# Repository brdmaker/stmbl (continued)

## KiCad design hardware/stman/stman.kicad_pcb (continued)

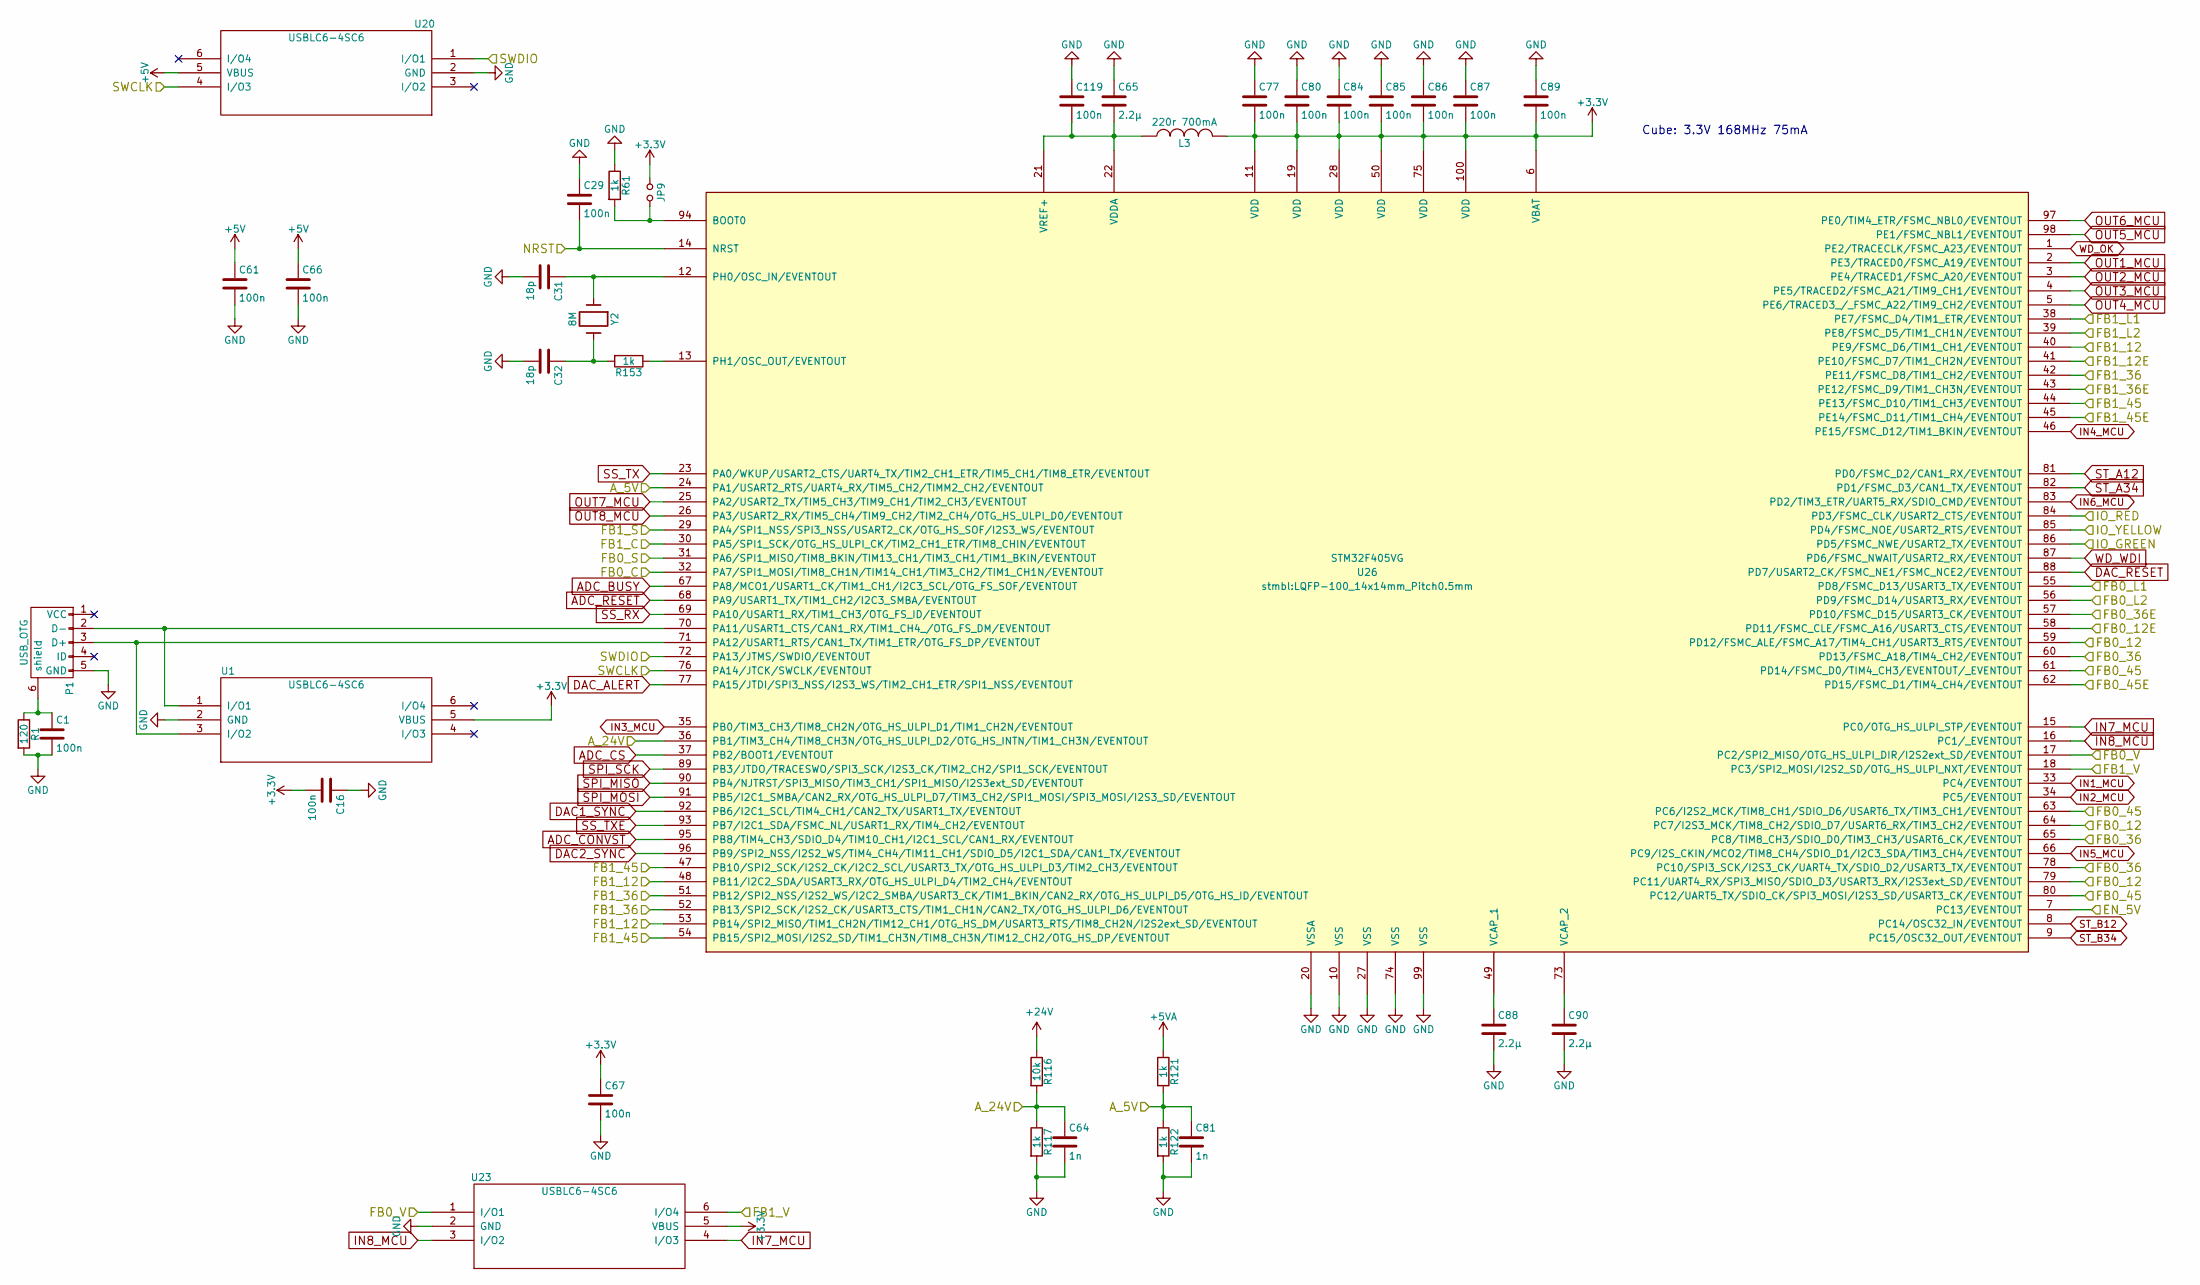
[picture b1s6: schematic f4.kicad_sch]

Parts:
C1, C16, C29, C61, C66, C67, C77, C80, C84, C85, C86, C87, C89, C119: 100n; C_0603; Voltage 50V; Tolerance X5R
C31, C32: 18p; C_0603; Voltage 50V; Tolerance X5R
C64, C81: 1n; C_0603; Voltage 50V; Tolerance X5R
C65, C88, C90: 2.2µ; C_0603; Voltage 35V; Tolerance X5R
JP9: Jumper_NO_Small; SOLDER_JUMPER
L3: 220r 700mA; R_0603
P1: USB_OTG; USB_Micro-B
R1: 120; R_0603; Tolerance 1%
R61, R117, R121, R122, R153: 1k; R_0603; Tolerance 1%
R116: 10k; R_0603; Tolerance 1%
U1, U20, U23: USBLC6-4SC6; SOT-23-6
U26: STM32F405VG; LQFP-100_14x14mm_Pitch0.5mm
Y2: 8M; Crystal_SMD_0503_4Pads

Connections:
+5V: C61.1, C66.1, U20.5 (VBUS); also elsewhere on the board
+5VA: R121.1; also elsewhere on the board
+24V: R116.1; also elsewhere on the board
/FB0/A12: U26.31 (PA6/SPI1_MISO/TIM8_BKIN/TIM13_CH1/TIM3_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); also elsewhere on the board
/FB0/A35: U26.32 (PA7/SPI1_MOSI/TIM8_CH1N/TIM14_CH1/TIM3_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); also elsewhere on the board
/FB0/A78: U23.1 (I/O1), U26.17 (PC2/SPI2_MISO/OTG_HS_ULPI_DIR/I2S2ext_S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); also elsewhere on the board
/FB0/D12: U26.59 (PD12/FSMC_ALE/FSMC_A17/TIM4_CH1/USART3_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), U26.64 (PC7/I2S3_MCK/TIM8_CH2/SDIO_D7/USART6_RX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), U26.79 (PC11/UART4_RX/SPI3_MISO/SDIO_D3/USART3_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); also elsewhere on the board
/FB0/D36: U26.60 (PD13/FSMC_A18/TIM4_CH2/EVENTOUT), U26.65 (PC8/TIM8_CH3/SDIO_D0/TIM3_CH3/USART6_CK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), U26.78 (PC10/SPI3_SCK/I2S3_CK/UART4_TX/SDIO_D2/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); also elsewhere on the board
/FB0/D45: U26.61 (PD14/FSMC_D0/TIM4_CH3/EVENTOUT/_EVENTOUT), U26.63 (PC6/I2S2_MCK/TIM8_CH1/SDIO_D6/USART6_TX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), U26.80 (PC12/UART5_TX/SDIO_CK/SPI3_MOSI/I2S3_SD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); also elsewhere on the board
/FB0/E12: U26.58 (PD11/FSMC_CLE/FSMC_A16/USART3_CTS/EVENT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); also elsewhere on the board
/FB0/E36: U26.57 (PD10/FSMC_D15/USART3_CK/EVENTOUT); also elsewhere on the board
/FB0/E45: U26.62 (PD15/FSMC_D1/TIM4_CH4/EVENTOUT); also elsewhere on the board
/FB0/L1: U26.55 (PD8/FSMC_D13/USART3_TX/EVENTOUT); also elsewhere on the board
/FB0/L2: U26.56 (PD9/FSMC_D14/USART3_RX/EVENTOUT); also elsewhere on the board
/FB1/A12: U26.29 (PA4/SPI1_NSS/SPI3_NSS/USART2_CK/OTG_HS_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); also elsewhere on the board
/FB1/A35: U26.30 (PA5/SPI1_SCK/OTG_HS_ULPI_CK/TIM2_CH1_ET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); also elsewhere on the board
/FB1/A78: U23.6 (I/O4), U26.18 (PC3/SPI2_MOSI/I2S2_SD/OTG_HS_ULPI_NXT/E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); also elsewhere on the board
/FB1/D12: U26.40 (PE9/FSMC_D6/TIM1_CH1/EVENTOUT), U26.48 (PB11/I2C2_SDA/USART3_RX/OTG_HS_ULPI_D4/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), U26.53 (PB14/SPI2_MISO/TIM1_CH2N/TIM12_CH1/OTG_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); also elsewhere on the board
/FB1/D36: U26.42 (PE11/FSMC_D8/TIM1_CH2/EVENTOUT), U26.51 (PB12/SPI2_NSS/I2S2_WS/I2C2_SMBA/USART3_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), U26.52 (PB13/SPI2_SCK/I2S2_CK/USART3_CTS/TIM1_C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); also elsewhere on the board
/FB1/D45: U26.44 (PE13/FSMC_D10/TIM1_CH3/EVENTOUT), U26.47 (PB10/SPI2_SCK/I2S2_CK/I2C2_SCL/USART3_T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), U26.54 (PB15/SPI2_MOSI/I2S2_SD/TIM1_CH3N/TIM8_C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); also elsewhere on the board
/FB1/E12: U26.41 (PE10/FSMC_D7/TIM1_CH2N/EVENTOUT); also elsewhere on the board
/FB1/E36: U26.43 (PE12/FSMC_D9/TIM1_CH3N/EVENTOUT); also elsewhere on the board
/FB1/E45: U26.45 (PE14/FSMC_D11/TIM1_CH4/EVENTOUT); also elsewhere on the board
/FB1/L1: U26.38 (PE7/FSMC_D4/TIM1_ETR/EVENTOUT); also elsewhere on the board
/FB1/L2: U26.39 (PE8/FSMC_D5/TIM1_CH1N/EVENTOUT); also elsewhere on the board
/IO/IO_GREEN: U26.86 (PD5/FSMC_NWE/USART2_TX/EVENTOUT); also elsewhere on the board
/IO/IO_RED: U26.84 (PD3/FSMC_CLK/USART2_CTS/EVENTOUT); also elsewhere on the board
/IO/IO_YELLOW: U26.85 (PD4/FSMC_NOE/USART2_RTS/EVENTOUT); also elsewhere on the board
/f4/A_5V: C81.1, R121.2, R122.1, U26.24 (PA1/USART2_RTS/UART4_RX/TIM5_CH2/TIMM2_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)
/f4/A_24V: C64.1, R116.2, R117.1, U26.36 (PB1/TIM3_CH4/TIM8_CH3N/OTG_HS_ULPI_D2/O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)
/f4/NRST: C29.2, U26.14 (NRST)
/f4/SWCLK: U20.4 (I/O3), U26.76 (PA14/JTCK/SWCLK/EVENTOUT)
/f4/SWDIO: U20.1 (I/O1), U26.72 (PA13/JTMS/SWDIO/EVENTOUT)
/supply/EN_5V: U26.7 (PC13/EVENTOUT); also elsewhere on the board
ADC_BUSY: U26.67 (PA8/MCO1/USART1_CK/TIM1_CH1/I2C3_SCL/OT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); also elsewhere on the board
ADC_CONVST: U26.95 (PB8/TIM4_CH3/SDIO_D4/TIM10_CH1/I2C1_SCL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); also elsewhere on the board
ADC_CS: U26.37 (PB2/BOOT1/EVENTOUT); also elsewhere on the board
ADC_RESET: U26.68 (PA9/USART1_TX/TIM1_CH2/I2C3_SMBA/EVENTO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); also elsewhere on the board
DAC1_SYNC: U26.92 (PB6/I2C1_SCL/TIM4_CH1/CAN2_TX/USART1_TX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); also elsewhere on the board
DAC2_SYNC: U26.96 (PB9/SPI2_NSS/I2S2_WS/TIM4_CH4/TIM11_CH1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); also elsewhere on the board
DAC_ALERT: U26.77 (PA15/JTDI/SPI3_NSS/I2S3_WS/TIM2_CH1_ETR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); also elsewhere on the board
DAC_RESET: U26.88 (PD7/USART2_CK/FSMC_NE1/FSMC_NCE2/EVENTO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); also elsewhere on the board
GND: C1.2, C16.1, C29.1, C31.2, C32.2, C61.2, C64.2, C65.1, C66.2, C67.2, C77.1, C80.1, C81.2, C84.1, C85.1, C86.1, C87.1, C88.2, C89.1, C90.2, C119.1, P1.5 (GND), R1.2, R61.1, R117.2, R122.2, U1.2 (GND), U20.2 (GND), U23.2 (GND), U26.10 (VSS), U26.20 (VSSA), U26.27 (VSS), U26.74 (VSS), U26.99 (VSS); also elsewhere on the board
IN1_MCU: U26.33 (PC4/EVENTOUT); also elsewhere on the board
IN2_MCU: U26.34 (PC5/EVENTOUT); also elsewhere on the board
IN3_MCU: U26.35 (PB0/TIM3_CH3/TIM8_CH2N/OTG_HS_ULPI_D1/T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); also elsewhere on the board
IN4_MCU: U26.46 (PE15/FSMC_D12/TIM1_BKIN/EVENTOUT); also elsewhere on the board
IN5_MCU: U26.66 (PC9/I2S_CKIN/MCO2/TIM8_CH4/SDIO_D1/I2C3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); also elsewhere on the board
IN6_MCU: U26.83 (PD2/TIM3_ETR/UART5_RX/SDIO_CMD/EVENTOUT); also elsewhere on the board
IN7_MCU: U23.4 (I/O3), U26.15 (PC0/OTG_HS_ULPI_STP/EVENTOUT); also elsewhere on the board
IN8_MCU: U23.3 (I/O2), U26.16 (PC1/_EVENTOUT); also elsewhere on the board
unnamed: C32.1, R153.2, Y2.2
unnamed: P1.3 (D+), U1.3 (I/O2), U26.71 (PA12/USART1_RTS/CAN1_TX/TIM1_ETR/OTG_FS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)
unnamed: P1.2 (D-), U1.1 (I/O1), U26.70 (PA11/USART1_CTS/CAN1_RX/TIM1_CH4_/OTG_F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)
unnamed: C1.1, P1.6 (shield), R1.1
unnamed: JP9.2, R61.2, U26.94 (BOOT0)
unnamed: C31.1, U26.12 (PH0/OSC_IN/EVENTOUT), Y2.1
unnamed: R153.1, U26.13 (PH1/OSC_OUT/EVENTOUT)
unnamed: C88.1, U26.49 (VCAP_1)
unnamed: C90.1, U26.73 (VCAP_2)
unnamed: C65.2, C119.2, L3.1, U26.21 (VREF+), U26.22 (VDDA)
OUT1_MCU: U26.2 (PE3/TRACED0/FSMC_A19/EVENTOUT); also elsewhere on the board
OUT2_MCU: U26.3 (PE4/TRACED1/FSMC_A20/EVENTOUT); also elsewhere on the board
OUT3_MCU: U26.4 (PE5/TRACED2/FSMC_A21/TIM9_CH1/EVENTOUT); also elsewhere on the board
OUT4_MCU: U26.5 (PE6/TRACED3_/_FSMC_A22/TIM9_CH2/EVENTOUT); also elsewhere on the board
OUT5_MCU: U26.98 (PE1/FSMC_NBL1/EVENTOUT); also elsewhere on the board
OUT6_MCU: U26.97 (PE0/TIM4_ETR/FSMC_NBL0/EVENTOUT); also elsewhere on the board
OUT7_MCU: U26.25 (PA2/USART2_TX/TIM5_CH3/TIM9_CH1/TIM2_CH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); also elsewhere on the board
OUT8_MCU: U26.26 (PA3/USART2_RX/TIM5_CH4/TIM9_CH2/TIM2_CH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); also elsewhere on the board
SPI_MISO: U26.90 (PB4/NJTRST/SPI3_MISO/TIM3_CH1/SPI1_MISO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); also elsewhere on the board
SPI_MOSI: U26.91 (PB5/I2C1_SMBA/CAN2_RX/OTG_HS_ULPI_D7/TI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); also elsewhere on the board
SPI_SCK: U26.89 (PB3/JTDO/TRACESWO/SPI3_SCK/I2S3_CK/TIM2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); also elsewhere on the board
SS_RX: U26.69 (PA10/USART1_RX/TIM1_CH3/OTG_FS_ID/EVENT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); also elsewhere on the board
SS_TX: U26.23 (PA0/WKUP/USART2_CTS/UART4_TX/TIM2_CH1_E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); also elsewhere on the board
SS_TXE: U26.93 (PB7/I2C1_SDA/FSMC_NL/USART1_RX/TIM4_CH2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); also elsewhere on the board
ST_A12: U26.81 (PD0/FSMC_D2/CAN1_RX/EVENTOUT); also elsewhere on the board
ST_A34: U26.82 (PD1/FSMC_D3/CAN1_TX/EVENTOUT); also elsewhere on the board
ST_B12: U26.8 (PC14/OSC32_IN/EVENTOUT); also elsewhere on the board
ST_B34: U26.9 (PC15/OSC32_OUT/EVENTOUT); also elsewhere on the board
WD_OK: U26.1 (PE2/TRACECLK/FSMC_A23/EVENTOUT); also elsewhere on the board
WD_WDI: U26.87 (PD6/FSMC_NWAIT/USART2_RX/EVENTOUT); also elsewhere on the board

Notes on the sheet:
Cube: 3.3V 168MHz 75mA

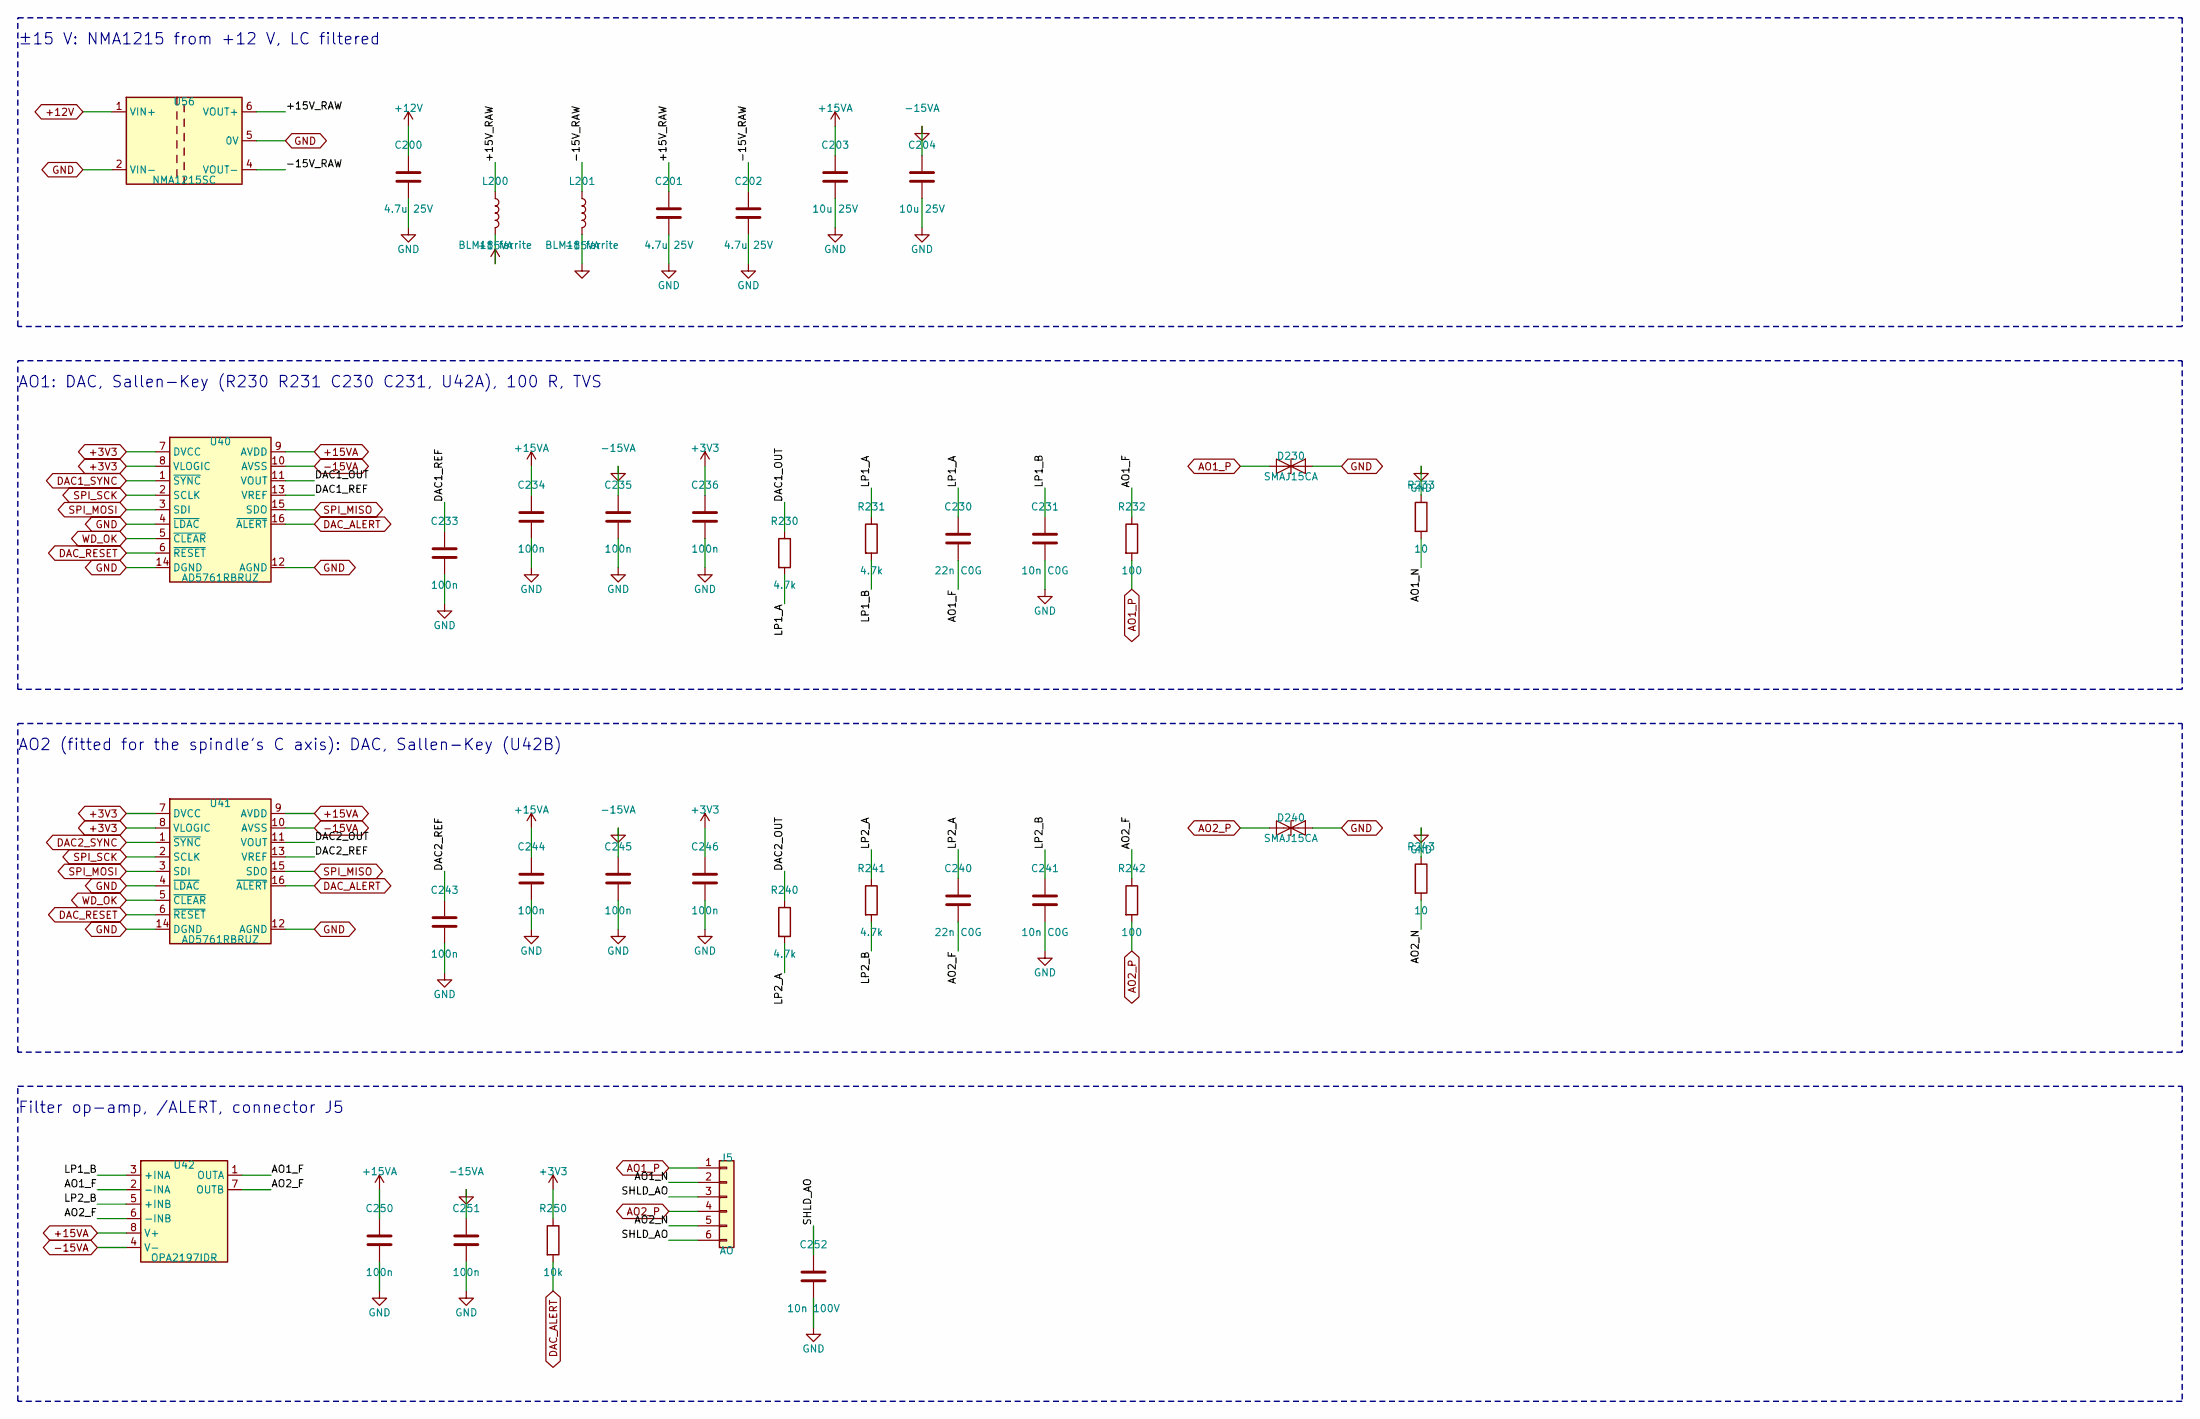
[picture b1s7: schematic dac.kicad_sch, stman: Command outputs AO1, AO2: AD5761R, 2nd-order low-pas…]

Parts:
C200, C201, C202: 4.7u 25V; C_0805_2012Metric
C203, C204: 10u 25V; C_1206_3216Metric
C230, C240: 22n C0G; C_0603_1608Metric
C231, C241: 10n C0G; C_0603_1608Metric
C233, C234, C235, C236, C243, C244, C245, C246, C250, C251: 100n; C_0603_1608Metric
C252: 10n 100V; C_0603_1608Metric
D230, D240: SMAJ15CA; D_SMA
J5: AO; PhoenixContact_MC_1,5_6-G-3.5_1x06_P3.50mm_Horizontal
L200, L201: BLM18 ferrite; L_0603_1608Metric
R230, R231, R240, R241: 4.7k; R_0603_1608Metric
R232, R242: 100; R_0603_1608Metric
R233, R243: 10; R_0603_1608Metric
R250: 10k; R_0603_1608Metric
U40, U41: AD5761RBRUZ; TSSOP-16_4.4x5mm_P0.65mm
U42: OPA2197IDR; SOIC-8_3.9x4.9mm_P1.27mm
U56: NMA1215SC; Converter_DCDC_Murata_NMAxxxxSC_THT

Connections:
+12V: C200.1, U56.1 (VIN+); also elsewhere on the board
+15VA: C203.1, C234.1, C244.1, C250.1, L200.2, U40.9 (AVDD), U41.9 (AVDD), U42.8 (V+); also elsewhere on the board
-15VA: C204.1, C235.1, C245.1, C251.1, L201.2, U40.10 (AVSS), U41.10 (AVSS), U42.4 (V-); also elsewhere on the board
/dac/+15V_RAW: C201.1, L200.1, U56.6 (VOUT+)
/dac/-15V_RAW: C202.1, L201.1, U56.4 (VOUT-)
/dac/AO1_F: C230.2, R232.1, U42.1 (OUTA), U42.2 (-INA)
/dac/AO1_N: J5.2, R233.2
/dac/AO2_F: C240.2, R242.1, U42.6 (-INB), U42.7 (OUTB)
/dac/AO2_N: J5.5, R243.2
/dac/DAC1_OUT: R230.1, U40.11 (VOUT)
/dac/DAC1_REF: C233.1, U40.13 (VREF)
/dac/DAC2_OUT: R240.1, U41.11 (VOUT)
/dac/DAC2_REF: C243.1, U41.13 (VREF)
/dac/LP1_A: C230.1, R230.2, R231.1
/dac/LP1_B: C231.1, R231.2, U42.3 (+INA)
/dac/LP2_A: C240.1, R240.2, R241.1
/dac/LP2_B: C241.1, R241.2, U42.5 (+INB)
/dac/SHLD_AO: C252.1, J5.3, J5.6
AO1_P: D230.1 (A1), J5.1, R232.2; also elsewhere on the board
AO2_P: D240.1 (A1), J5.4, R242.2; also elsewhere on the board
DAC1_SYNC: U40.1 (~SYNC); also elsewhere on the board
DAC2_SYNC: U41.1 (~SYNC); also elsewhere on the board
DAC_ALERT: R250.2, U40.16 (~ALERT), U41.16 (~ALERT); also elsewhere on the board
DAC_RESET: U40.6 (~RESET), U41.6 (~RESET); also elsewhere on the board
GND: C200.2, C201.2, C202.2, C203.2, C204.2, C231.2, C233.2, C234.2, C235.2, C236.2, C241.2, C243.2, C244.2, C245.2, C246.2, C250.2, C251.2, C252.2, D230.2 (A2), D240.2 (A2), R233.1, R243.1, U40.4 (~LDAC), U40.12 (AGND), U40.14 (DGND), U41.4 (~LDAC), U41.12 (AGND), U41.14 (DGND), U56.2 (VIN-), U56.5 (0V); also elsewhere on the board
SPI_MISO: U40.15 (SDO), U41.15 (SDO); also elsewhere on the board
SPI_MOSI: U40.3 (SDI), U41.3 (SDI); also elsewhere on the board
SPI_SCK: U40.2 (SCLK), U41.2 (SCLK); also elsewhere on the board
WD_OK: U40.5 (~CLEAR), U41.5 (~CLEAR); also elsewhere on the board

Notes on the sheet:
±15 V: NMA1215 from +12 V, LC filtered
AO1: DAC, Sallen-Key (R230 R231 C230 C231, U42A), 100 R, TVS
AO2 (fitted for the spindle's C axis): DAC, Sallen-Key (U42B)
Filter op-amp, /ALERT, connector J5

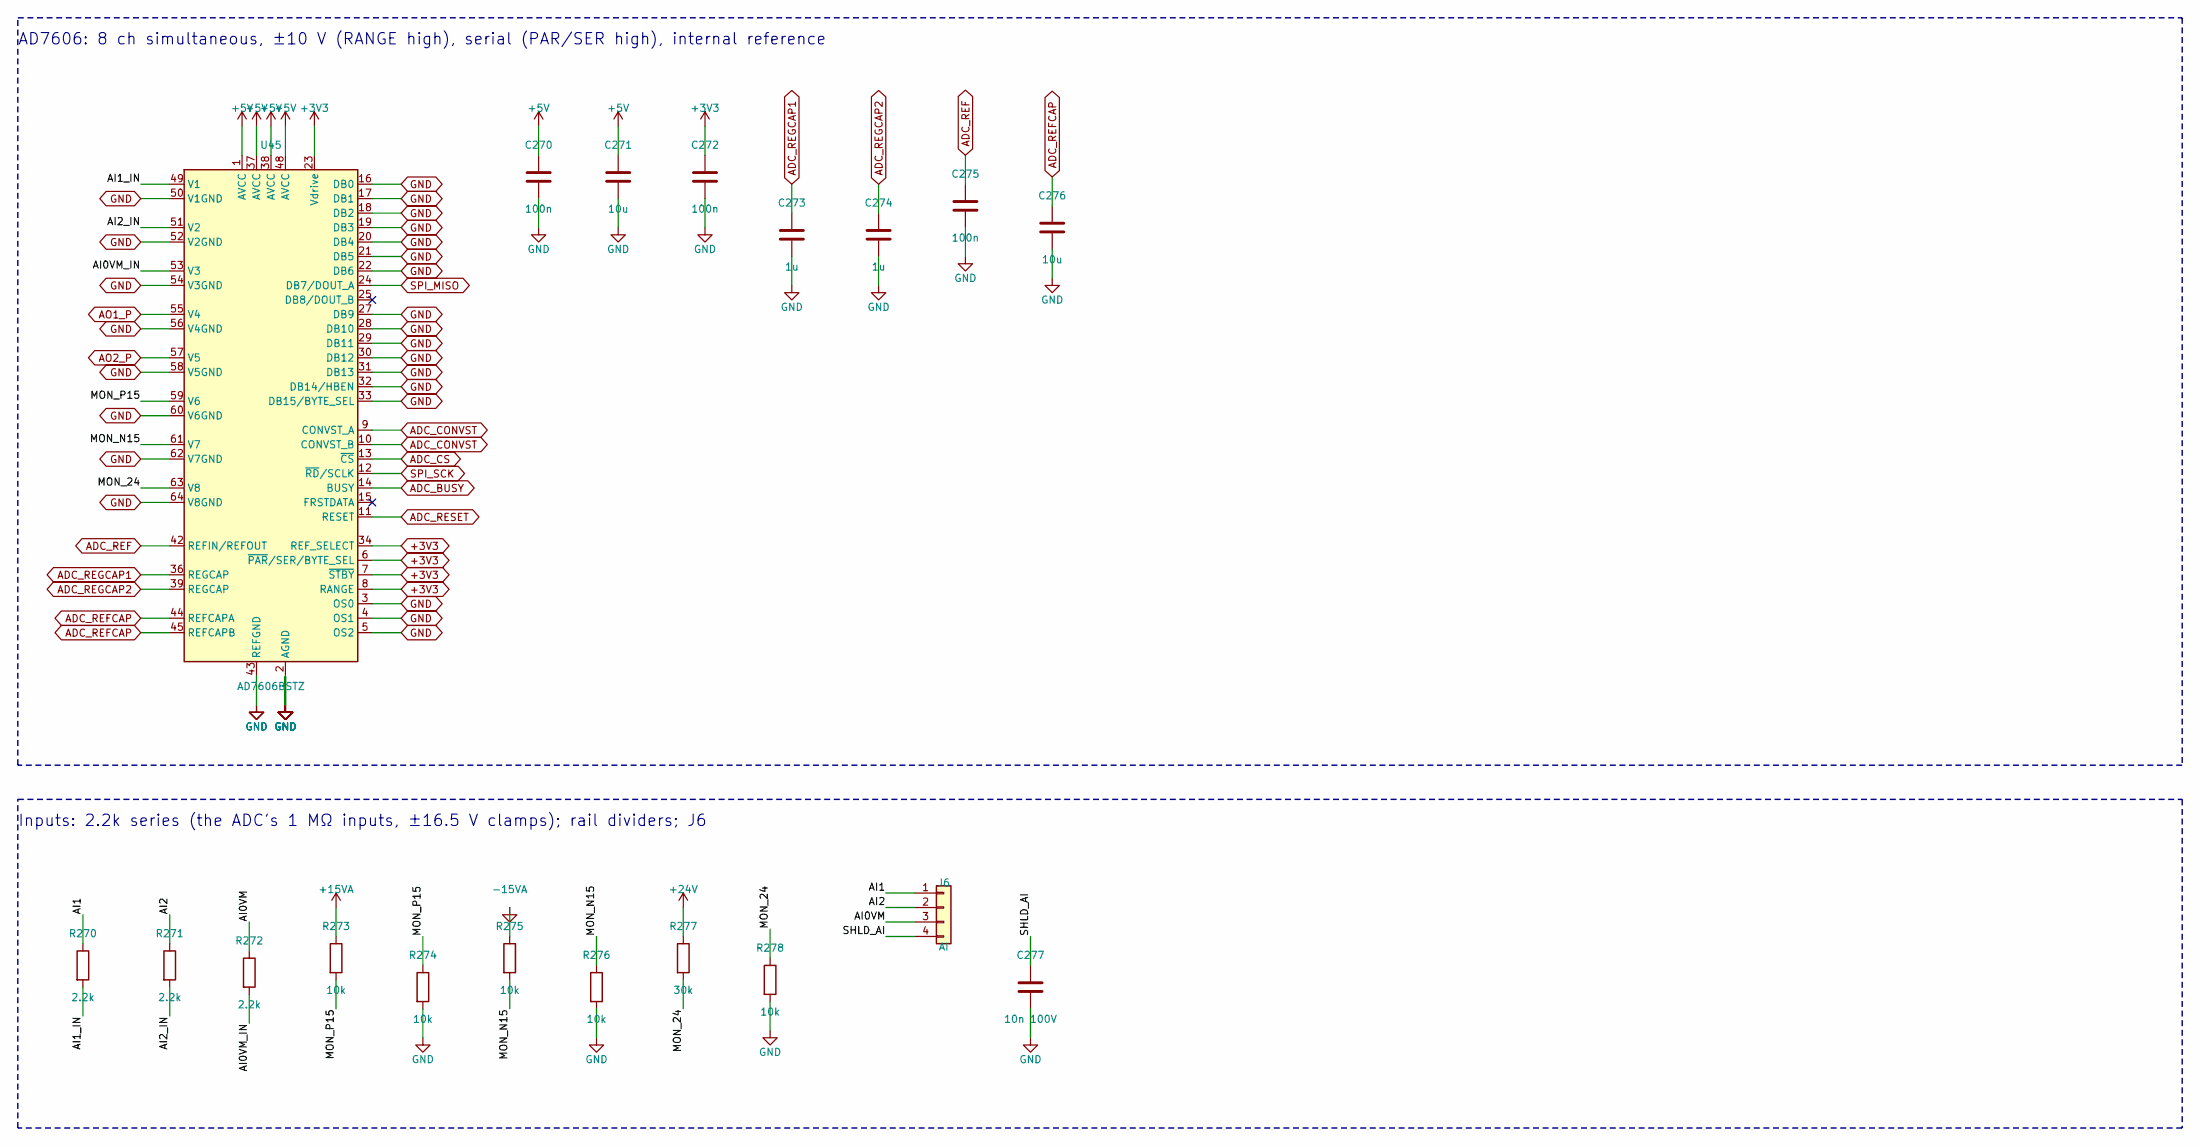
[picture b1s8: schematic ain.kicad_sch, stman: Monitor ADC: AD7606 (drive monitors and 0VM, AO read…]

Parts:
C270, C272, C275: 100n; C_0603_1608Metric
C271, C276: 10u; C_0805_2012Metric
C273, C274: 1u; C_0603_1608Metric
C277: 10n 100V; C_0603_1608Metric
J6: AI; PhoenixContact_MC_1,5_4-G-3.5_1x04_P3.50mm_Horizontal
R270, R271, R272: 2.2k; R_0603_1608Metric
R273, R274, R275, R276, R278: 10k; R_0603_1608Metric
R277: 30k; R_0603_1608Metric
U45: AD7606BSTZ; LQFP-64_10x10mm_P0.5mm

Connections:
+5V: C270.1, C271.1, U45.1 (AVCC), U45.37 (AVCC), U45.38 (AVCC), U45.48 (AVCC); also elsewhere on the board
+15VA: R273.1; also elsewhere on the board
+24V: R277.1; also elsewhere on the board
-15VA: R275.1; also elsewhere on the board
/ain/AI0VM: J6.3, R272.1
/ain/AI0VM_IN: R272.2, U45.53 (V3)
/ain/AI1: J6.1, R270.1
/ain/AI1_IN: R270.2, U45.49 (V1)
/ain/AI2: J6.2, R271.1
/ain/AI2_IN: R271.2, U45.51 (V2)
/ain/MON_24: R277.2, R278.1, U45.63 (V8)
/ain/MON_N15: R275.2, R276.1, U45.61 (V7)
/ain/MON_P15: R273.2, R274.1, U45.59 (V6)
/ain/SHLD_AI: C277.1, J6.4
ADC_BUSY: U45.14 (BUSY); also elsewhere on the board
ADC_CONVST: U45.9 (CONVST_A), U45.10 (CONVST_B); also elsewhere on the board
ADC_CS: U45.13 (~CS); also elsewhere on the board
ADC_REF: C275.1, U45.42 (REFIN/REFOUT)
ADC_REFCAP: C276.1, U45.44 (REFCAPA), U45.45 (REFCAPB)
ADC_REGCAP1: C273.1, U45.36 (REGCAP)
ADC_REGCAP2: C274.1, U45.39 (REGCAP)
ADC_RESET: U45.11 (RESET); also elsewhere on the board
AO1_P: U45.55 (V4); also elsewhere on the board
AO2_P: U45.57 (V5); also elsewhere on the board
GND: C270.2, C271.2, C272.2, C273.2, C274.2, C275.2, C276.2, C277.2, R274.2, R276.2, R278.2, U45.2 (AGND), U45.3 (OS0), U45.4 (OS1), U45.5 (OS2), U45.16 (DB0), U45.17 (DB1), U45.18 (DB2), U45.19 (DB3), U45.20 (DB4), U45.21 (DB5), U45.22 (DB6), U45.26 (AGND), U45.27 (DB9), U45.28 (DB10), U45.29 (DB11), U45.30 (DB12), U45.31 (DB13), U45.32 (DB14/HBEN), U45.33 (DB15/BYTE_SEL), U45.35 (AGND), U45.40 (AGND), U45.41 (AGND), U45.43 (REFGND), U45.46 (REFGND), U45.47 (AGND), U45.50 (V1GND), U45.52 (V2GND), U45.54 (V3GND), U45.56 (V4GND), U45.58 (V5GND), U45.60 (V6GND), U45.62 (V7GND), U45.64 (V8GND); also elsewhere on the board
SPI_MISO: U45.24 (DB7/DOUT_A); also elsewhere on the board
SPI_SCK: U45.12 (~RD/SCLK); also elsewhere on the board

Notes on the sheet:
AD7606: 8 ch simultaneous, ±10 V (RANGE high), serial (PAR/SER high), internal reference
Inputs: 2.2k series (the ADC's 1 MΩ inputs, ±16.5 V clamps); rail dividers; J6

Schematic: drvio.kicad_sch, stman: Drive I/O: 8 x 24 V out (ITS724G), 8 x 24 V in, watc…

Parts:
C280, C281: 100n 50V; C_0603_1608Metric
C282, C285: 100n; C_0603_1608Metric
C290, C292, C294, C296, C298, C300, C302, C304: 1n; C_0603_1608Metric
D290, D292, D294, D296, D298, D300, D302, D304: BAT54S; SOT-23
J7: OUT; PhoenixContact_MC_1,5_10-G-3.5_1x10_P3.50mm_Horizontal
J8: IN; PhoenixContact_MC_1,5_10-G-3.5_1x10_P3.50mm_Horizontal
R280, R281, R282, R283, R284, R285, R286, R291, R293, R295, R297, R299, R301, R303, R305: 10k; R_0603_1608Metric
R290, R292, R294, R296, R298, R300, R302, R304: 47k; R_0603_1608Metric
U50, U51: ITS724G; SOIC-20W_7.5x12.8mm_P1.27mm
U55: 74LVC2G08; SOT-23-8
U57: MAX6369KA+T; SOT-23-8

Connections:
+24V: C280.1, C281.1, J8.9, J8.10, U50.1 (VBB), U50.10 (VBB), U50.11 (VBB), U50.12 (VBB), U50.15 (VBB), U50.16 (VBB), U50.19 (VBB), U50.20 (VBB), U51.1 (VBB), U51.10 (VBB), U51.11 (VBB), U51.12 (VBB), U51.15 (VBB), U51.16 (VBB), U51.19 (VBB), U51.20 (VBB); also elsewhere on the board
/drvio/IN1: J8.1, R290.1
/drvio/IN2: J8.2, R292.1
/drvio/IN3: J8.3, R294.1
/drvio/IN4: J8.4, R296.1
/drvio/IN5: J8.5, R298.1
/drvio/IN6: J8.6, R300.1
/drvio/IN7: J8.7, R302.1
/drvio/IN8: J8.8, R304.1
/drvio/OUT1: J7.1, U50.18 (OUT1)
/drvio/OUT1_IN: U50.3 (IN1), U55.7 (1Y)
/drvio/OUT2: J7.2, U50.17 (OUT2)
/drvio/OUT2_IN: U50.5 (IN2), U55.3 (2Y)
/drvio/OUT3: J7.3, U50.14 (OUT3)
/drvio/OUT4: J7.4, U50.13 (OUT4)
/drvio/OUT5: J7.5, U51.18 (OUT1)
/drvio/OUT6: J7.6, U51.17 (OUT2)
/drvio/OUT7: J7.7, U51.14 (OUT3)
/drvio/OUT8: J7.8, U51.13 (OUT4)
GND: C280.2, C281.2, C282.2, C285.2, C290.2, C292.2, C294.2, C296.2, C298.2, C300.2, C302.2, C304.2, D290.1 (A), D292.1 (A), D294.1 (A), D296.1 (A), D298.1 (A), D300.1 (A), D302.1 (A), D304.1 (A), J7.9, J7.10, R280.2, R281.2, R291.2, R293.2, R295.2, R297.2, R299.2, R301.2, R303.2, R305.2, U50.2 (GND1/2), U50.6 (GND3/4), U51.2 (GND1/2), U51.6 (GND3/4), U55.4 (GND), U57.2 (GND), U57.5 (SET1), U57.6 (SET2); also elsewhere on the board
IN1_MCU: C290.1, D290.3 (COM), R290.2, R291.1; also elsewhere on the board
IN2_MCU: C292.1, D292.3 (COM), R292.2, R293.1; also elsewhere on the board
IN3_MCU: C294.1, D294.3 (COM), R294.2, R295.1; also elsewhere on the board
IN4_MCU: C296.1, D296.3 (COM), R296.2, R297.1; also elsewhere on the board
IN5_MCU: C298.1, D298.3 (COM), R298.2, R299.1; also elsewhere on the board
IN6_MCU: C300.1, D300.3 (COM), R300.2, R301.1; also elsewhere on the board
IN7_MCU: C302.1, D302.3 (COM), R302.2, R303.1; also elsewhere on the board
IN8_MCU: C304.1, D304.3 (COM), R304.2, R305.1; also elsewhere on the board
OUT1_MCU: R280.1, U55.1 (1A); also elsewhere on the board
OUT2_MCU: R281.1, U55.5 (2A); also elsewhere on the board
OUT3_MCU: U50.7 (IN3); also elsewhere on the board
OUT4_MCU: U50.9 (IN4); also elsewhere on the board
OUT5_MCU: U51.3 (IN1); also elsewhere on the board
OUT6_MCU: U51.5 (IN2); also elsewhere on the board
OUT7_MCU: U51.7 (IN3); also elsewhere on the board
OUT8_MCU: U51.9 (IN4); also elsewhere on the board
ST_A12: R282.2, U50.4 (ST1/2); also elsewhere on the board
ST_A34: R283.2, U50.8 (ST3/4); also elsewhere on the board
ST_B12: R284.2, U51.4 (ST1/2); also elsewhere on the board
ST_B34: R285.2, U51.8 (ST3/4); also elsewhere on the board
WD_OK: R286.2, U55.2 (1B), U55.6 (2B), U57.7 (~WDO); also elsewhere on the board
WD_WDI: U57.1 (WDI); also elsewhere on the board

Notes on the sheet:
Outputs: ITS724G x2, OUT1/OUT2 gated by the watchdog
Watchdog MAX6369: WD_OK low -> DACs to 0 V, OUT1/OUT2 off
Inputs: 47k / 10k, 1 nF, BAT54S clamp (high > ~13 V, low < ~6 V)

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
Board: 4 copper layers, 342 parts (64 on the bottom side), 213 nets, no tracks yet.

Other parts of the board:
REF1, REF2: Fiducial_1mm_Dia_2.54mm_Outer_CopperTop; Fiducial_1mm_Outer_CopperTop
